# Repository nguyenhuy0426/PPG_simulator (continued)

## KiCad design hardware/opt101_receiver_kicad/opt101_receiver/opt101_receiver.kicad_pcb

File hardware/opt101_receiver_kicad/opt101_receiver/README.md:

> Gá mới: thanh chữ U không bắt vít, hai biến thể riêng theo receiver. Xem `mechanical/README.md`.

# PCB thu PPG — OPT101P ×2, 70 × 20 mm

Mở **`opt101_receiver.kicad_pro` bằng KiCad 10**, rồi mở schematic hoặc PCB.
Thiết kế đã đi dây hai lớp, có thư viện symbol, footprint và mô hình 3D cục bộ.
Ảnh `reports/pcb_top.png` hiển thị **socket trống**, chưa cắm IC OPT101P.
Mặt sau có silkscreen `DATN: PPG-Simulator` và
`Nguyen Nhat Huy - Pham Thanh Vy`; xem `reports/pcb_bottom.png`.
Mặt sau cũng ghi tên tín hiệu tại từng pad J1/J2/J3 và từng hàng chân của
hai socket OPT101. Các nhãn này không dùng số thứ tự chân; `R/I` là hai đầu
ra, `V` là 3,3 V, `GR/GI` là ground theo kênh, `FB` là hồi tiếp và `NC` để hở.

## Linh kiện và kết nối

| Ref | Linh kiện / quy cách | Số lượng |
|---|---|---:|
| U1, U2 | OPT101P dạng PDIP-8, cắm socket DIP-8 rộng 7,62 mm, bước chân 2,54 mm | 2 IC + 2 socket |
| C1, C2 | Tụ gốm dán **100 nF, 50 V, X7R, 0805**, không phân cực | 2 |
| R1, R2 | 1 kΩ 1%, SMD 0805, lọc ngõ ra | 2 |
| C3, C4 | 1 µF X7R 16 V, SMD 0805, không phân cực | 2 |
| J1, J2 | Header đực thẳng 1×4, bước 2,00 mm | 2 |
| J3 | Header đực thẳng 1×2, bước 2,54 mm | 1 |

Socket chỉ nhận **PDIP có chân xuyên lỗ**. OPT101 dạng SOP chân cong J không
cắm trực tiếp được. Đối chiếu package thực trước khi tháo IC khỏi module tím.
Rãnh socket và dấu pin 1 của IC hướng về cạnh trên có chữ RED/A2, IR/A0.

U1 là **Red → A2**, U2 là **IR → A0**. Với từng IC:

- Chân 1 → nguồn 3,3 V từ Grove; tụ 100 nF nối nguồn với GND ngay cạnh socket.
- Chân 3 và 8 → GND.
- Chân 4 nối trực tiếp chân 5 bằng đường đồng để dùng hồi tiếp 1 MΩ trong IC.
- Chân 2, 6, 7 để hở có chủ ý; không gắn điện trở 1 MΩ ngoài.

**J1/J2**, đọc theo số pad, từ pad vuông sang phải khi nhìn mặt linh kiện:

| Chân | J1 → socket A2 trên HAT | J2 → socket A0 trên HAT |
|---|---|---|
| 1 — SIG | OUT_RED | OUT_IR |
| 2 — NC | Không nối | Không nối |
| 3 — 3V3 | Nguồn 3,3 V | Nguồn 3,3 V |
| 4 — GND | GND | GND |

Pinout theo chuẩn Grove analog: pin 1 tín hiệu chính, pin 2 tín hiệu phụ,
pin 3 nguồn, pin 4 GND. Đây là **header trần bước 2 mm**, không phải socket
Grove có khóa. Kiểm tra thứ tự dây đến HAT trước khi cắm; không suy ra chiều
cắm chỉ từ màu dây. Chân phụ A1/A3 không được nối vào mạch.

C1/C2 là tụ bypass nguồn, **không phân cực**. Điện áp mạch chỉ 3,3 V nhưng
chọn loại 50 V X7R cỡ 0805. Loại 25 V X7R cỡ 0805 cũng dùng được về điện;
không thay bằng tụ điện phân vì tác dụng bypass cao tần khác nhau.

Mỗi kênh có đường nguồn và vùng GND riêng trên PCB; hai GND chung tại HAT.
Cắm cả hai cáp Grove để cấp nguồn đủ hai kênh. Không cấp 5 V vào board.

**J3 cho ADS1115**:

| Chân | Tín hiệu | Cách nối dự kiến |
|---|---|---|
| 1 — pad vuông, RED | OUT_RED, sau R1, cùng net J1.1 | ADS1115 AIN0 |
| 2 — IR | OUT_IR, sau R2, cùng net J2.1 | ADS1115 AIN1 |

J3 là ngõ lấy tín hiệu song song, không có buffer, không có nguồn hoặc GND.
ADS1115 cần được cấp nguồn riêng phù hợp và **nối GND về cùng GND HAT/Pi**.
Việc cấp nguồn OPT101 vẫn qua J1/J2. Hai đầu ra không phải một cặp vi sai:
đọc từng kênh so với GND. Cấu hình ADC, I²C và phần mềm ADS1115 chưa thuộc
thiết kế này. Nên dùng dây tín hiệu ngắn, đi sát dây GND; tải của ADC/cáp và
việc đọc đồng thời với Grove chưa được thử trên phần cứng.

## Kích thước và khớp mô hình 3D

PCB v1.5: **70 × 20 × 1,6 mm**, không có lỗ bắt vít. Tính từ góc trên trái:
- Tâm OPT101: (15,75; 7,81) và (54,25; 7,81) mm.
- J1/J2: chân đầu tại X=13/51 mm, Y=16,5 mm; bước 2 mm.
- J3: X=26/28,54 mm, Y=16,5 mm.

Đường đồng ngang/dọc; R1/R2 và C3/C4 ở mặt sau, C1/C2 sát socket ở mặt trước.
Gá riêng `mechanical/frame_70x20_print.stl` giữ mặt PCB tại X thế giới 137,5 mm,
bậc đỡ Y=19,81 mm; tâm quang vẫn Y=32 mm, Z=±19,25 mm. Hai kênh cách 38,5 mm.
Gá không bắt vít; giữ board và bịt khe/vách giữa bằng băng keo cách điện đục quang.
Không dùng gá BPW34 thay gá OPT101 vì vị trí cảm biến theo cạnh ngắn khác nhau.

### Kiểm tra đường ánh sáng và khẩu độ

Kiểm tra boolean dùng trực tiếp STL thân hộp, nắp, các tấm khẩu độ và khung PCB
mới đạt **20/20 phép thử hình học**. Ở vị trí danh nghĩa, trục của LED Red và
IR đều đi qua tâm lỗ khẩu độ tại X = 114,2 mm rồi đến tâm vùng nhạy của OPT101
tương ứng. Tia thẳng từ LED này hướng tới cảm biến kia cắt vách ngăn đặc giữa
hai buồng, nên không có đường nhìn thẳng xuyên kênh.

- Tấm `blank` chặn tia trục của cả hai kênh.
- Lỗ Ø2, Ø5 và Ø16 đều cho tia trục đi qua.
- Vùng nhạy OPT101 là 2,29 × 2,29 mm. Khi chiếu ngược các góc vùng nhạy lên
  mặt khẩu độ, bán kính góc lớn nhất là khoảng 0,99 mm cho Red và 1,40 mm cho
  IR. Vì vậy Ø2 chỉ vừa đủ cho Red và cắt các góc vùng nhạy IR; **Ø5 hoặc Ø16
  phủ toàn bộ vùng nhạy danh nghĩa của cả hai kênh**.
- Bán kính chùm tại mức nửa cường độ trong mô hình nguồn lớn hơn các lỗ khẩu
  độ, nên khẩu độ chủ động giới hạn lượng sáng. Kiểm tra này xác nhận đường
  nhìn và độ phủ hình học, không dự đoán công suất quang hoặc biên độ tín hiệu.

Kết luận phụ thuộc vào tâm package danh nghĩa và khoảng X cửa sổ cảm biến
126,5–132,0 mm lấy từ bao socket + IC. Sai số tâm die, chiều cao socket thật,
độ trong của nhựa in, phản xạ mặt trong và khe lắp chưa được mô phỏng. Sau khi
in cần thử lần lượt với tấm `blank` và Ø5: `blank` phải cho mức tối gần như nhau
khi LED bật/tắt, còn Ø5 phải tạo đáp ứng rõ chỉ ở đúng kênh.

### Thay đổi mốc khoảng cách quang

Mô hình cũ đặt cửa sổ module tại X = 120 mm nhờ module tím và trụ đỡ.
Cắm IC trực tiếp lên socket của PCB **không giữ nguyên mốc 120 mm**.
Gọi `h` là khoảng cách đo vuông góc từ mặt linh kiện PCB đến cửa sổ quang
của IC đã cắm hết vào socket:

```
X_cửa_sổ_mới = 137,5 - h
d_thực = d_theo_thang_cũ + 17,5 - h
```

Ví dụ **chỉ để minh họa**, nếu đo h = 8,3 mm thì d thực tăng 9,2 mm.
Không dùng ví dụ này như kích thước bảo đảm của socket. Mã mô hình cũ và
thang khoảng cách cũ chưa được đổi; phải đo lại h và hiệu chuẩn khoảng cách.
Không đưa board ra trước để cố giữ X=120 vì board liền sẽ đụng vách ngăn giữa.

## Kiểm tra và giới hạn

Kiểm tra bằng **KiCad 10.0.6**: ERC 0 lỗi/0 cảnh báo; DRC 0 vi phạm,
0 pad chưa nối, 0 lỗi parity; 152 kiểm tra hợp đồng chân, kích thước,
hình học đường đồng đạt.
Kiểm tra cơ khí: 386/386 đạt với bao linh kiện đã nêu; khung là một khối kín.
Kiểm tra đường quang danh nghĩa: 20/20 đạt.

- `reports/erc.rpt`: ERC schematic.
- `reports/drc.rpt`: DRC, vùng đồng đã đổ, kiểm tra parity với schematic.
- `reports/pin_contract.json`: kiểm tra độc lập chân điện, bước header/socket,
  kích thước board và khoảng cách hai làn.
- `mechanical/fit_report.json`: kiểm tra boolean với **STL thân/nắp đã xuất
  trong source**, gồm đường đưa cụm từ trên xuống theo bước 2 mm.
- `mechanical/optical_report.json`: kết quả định lượng đường tia, độ che của
  từng khẩu độ và chặn tia chéo giữa hai kênh.
- `mechanical/optical_alignment.png`: hình diễn giải vị trí LED, khẩu độ và
  khoảng cửa sổ OPT101 theo trục X.

Kiểm tra cơ khí dùng bao linh kiện: socket + IC cao tối đa 11 mm, header
cao tối đa 12 mm, tụ cao tối đa 7 mm phía trước PCB. Chọn linh kiện trong
các bao này. Đầu cáp mềm chưa được mô hình hóa. Kiểm tra CAD không thay thế
thử lắp bản in, kiểm tra rò sáng, đo điện hoặc hiệu chuẩn quang thực tế.

Các kết quả phần cứng chưa thực hiện: nguồn thật, cắm socket, mức tín hiệu,
nhiễu, bão hòa, Grove ADC và ADS1115. ERC/DRC sạch không phải chứng minh
đã đo được tín hiệu PPG trên mạch thật.

## File gia công

`fabrication/` chứa Gerber hai lớp đồng, soldermask hai mặt, silkscreen và
Edge.Cuts, kèm Excellon tách PTH/NPTH. Số lượng/cỡ lỗ khoan theo `reports/drill.rpt`; receiver không còn lỗ bắt vít. Chọn FR4 dày 1,6 mm,
đồng 1 oz, 70 × 20 mm; không yêu cầu trở kháng kiểm soát.
File này đã xuất nhưng **chưa được gửi đặt sản xuất**. Kiểm tra package IC,
socket, đầu cáp và bản in khung thật trước khi chốt gia công.

## Tái sinh

Không cần chạy script để mở hoặc chỉnh file trong KiCad. `generate_design.py`
**ghi đè** thiết kế đã sinh; chỉ chạy lại nếu muốn tái tạo từ mã tham số.

```bash
python-with-pcbnew generate_design.py --kicad-share /path/to/share/kicad --cli /path/to/kicad-cli
kicad-cli sch erc opt101_receiver.kicad_sch -o reports/erc.rpt
kicad-cli pcb drc opt101_receiver.kicad_pcb --refill-zones --save-board --schematic-parity -o reports/drc.rpt
python-with-pcbnew verify_design.py
# Từ gốc repository:
.cad_venv/bin/python hardware/opt101_receiver_kicad/opt101_receiver/mechanical/build_adapter.py
.cad_venv/bin/python hardware/opt101_receiver_kicad/opt101_receiver/mechanical/optical_check.py
```

Nguồn kỹ thuật:

- [TI OPT101 datasheet, pinout và hồi tiếp](https://www.ti.com/lit/ds/symlink/opt101.pdf), trang 3, 13 và 23.
- [Seeed Grove System](https://wiki.seeedstudio.com/Grove_System/), pinout Grove analog.
- [Grove Base HAT for Raspberry Pi](https://wiki.seeedstudio.com/Grove_Base_Hat_for_Raspberry_Pi/), analog 3,3 V.
- Sơ đồ gốc: `docs/hardware/PPG_PROTOTYPE_SCHEMATIC.md`, phần RX.

Footprint và mô hình 3D được sao chép từ thư viện KiCad 10, đổi tên thư viện
thành PPG và dùng đường dẫn tương đối để dự án có thể chuyển máy.
Thư viện KiCad dùng CC-BY-SA 4.0 với ngoại lệ sử dụng trong thiết kế điện tử:
[KiCad Library License](https://www.kicad.org/libraries/license/).

## Schematic v1.5 — lọc ngõ ra

Hai kênh được vẽ bằng dây nối trực tiếp từ Grove qua nguồn/bypass tới OPT101,
strap 4–5, rồi qua R1/R2 = 1 kΩ tới Grove/J3; C3/C4 = 1 µF nối từ OUT sau điện trở xuống GND từng kênh. Bộ lọc có fc danh nghĩa 159 Hz, suy hao khoảng 0,8% tại 20 Hz; không phải lọc notch 50 Hz. Với nguồn 3,3 V, OPT101 không rail-to-rail: cần chừa headroom khoảng 1,15–1,3 V phía nguồn dương. Xem `reports/schematic.pdf` và `reports/schematic.png`. Giao cắt không
có dấu chấm không nối điện.

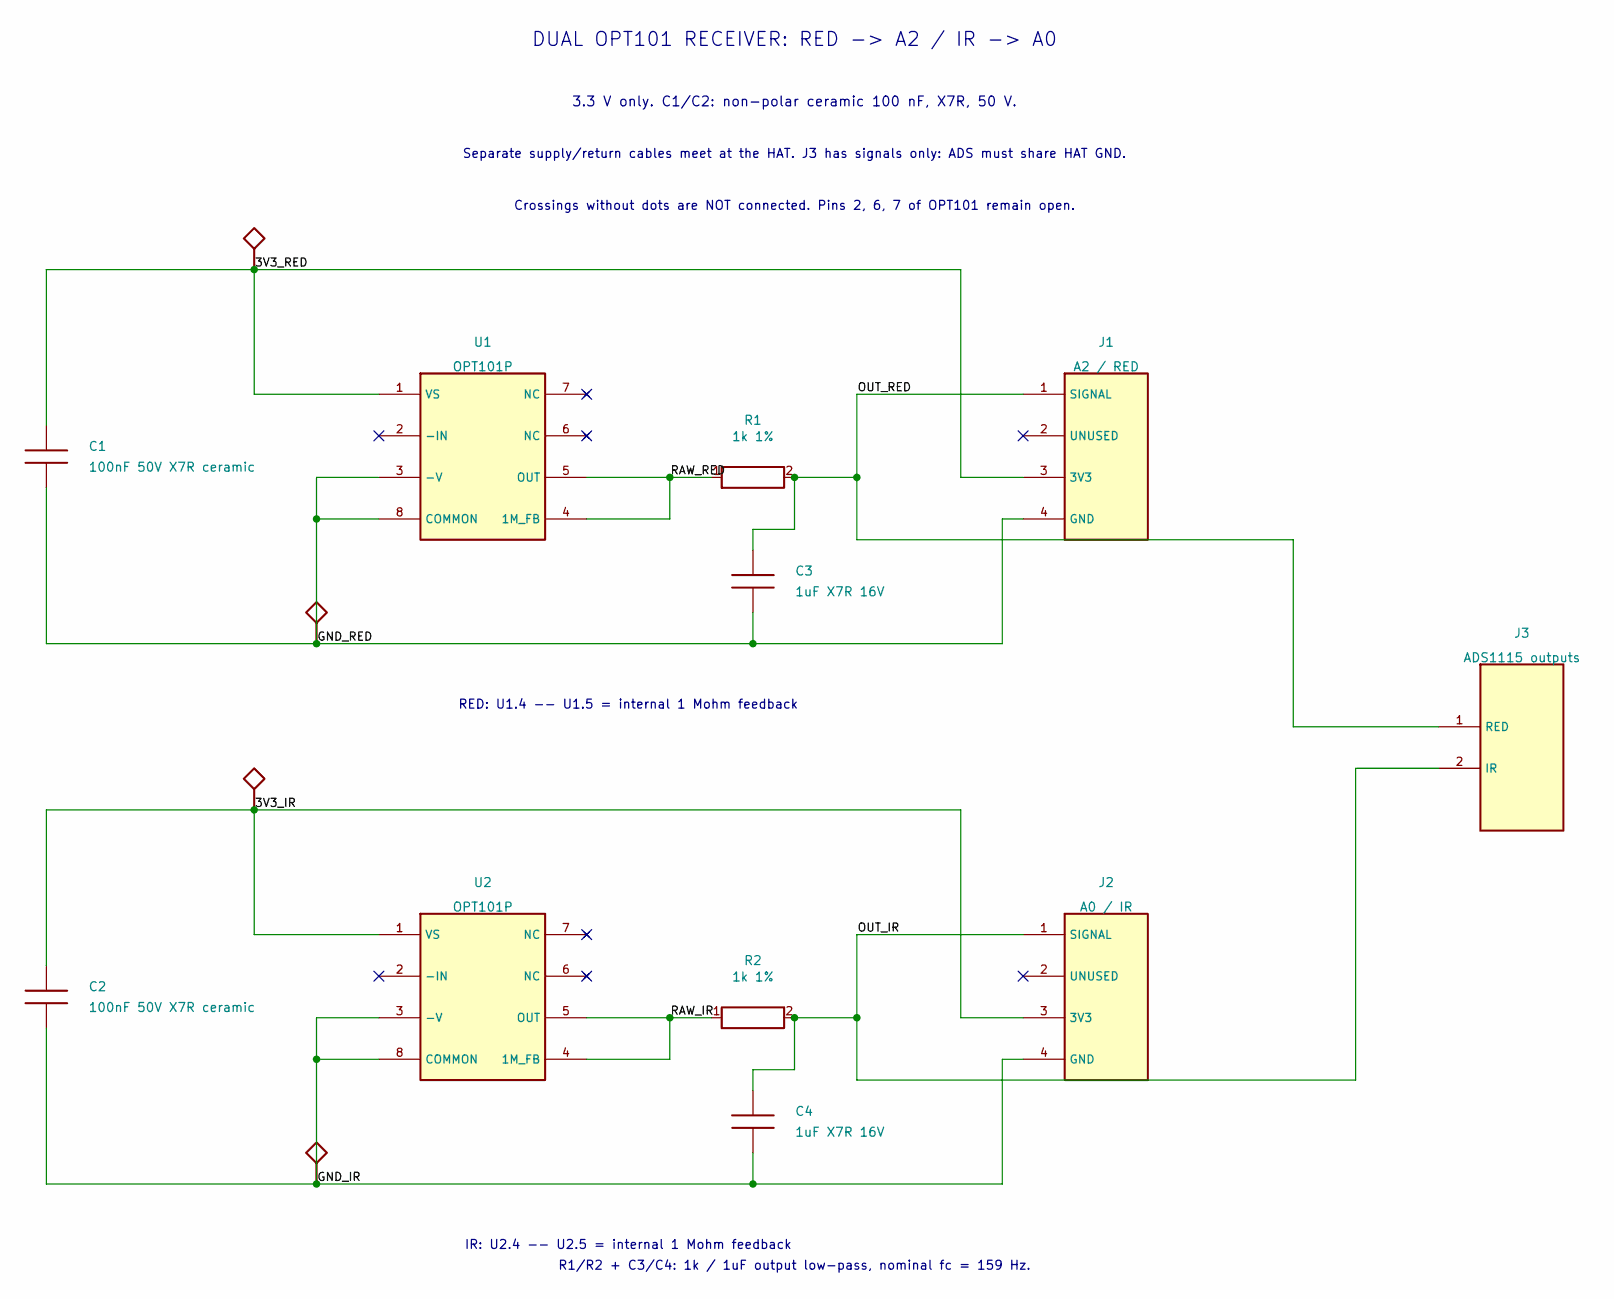
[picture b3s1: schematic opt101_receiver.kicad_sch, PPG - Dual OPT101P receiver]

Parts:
C1, C2: 100nF 50V X7R ceramic; C0805_Hand
C3, C4: 1uF X7R 16V; C0805_Hand
J1: A2 / RED; Header_1x04_P2mm
J2: A0 / IR; Header_1x04_P2mm
J3: ADS1115 outputs; Header_1x02_P2.54mm
R1, R2: 1k 1%; R0805_Hand
U1, U2: OPT101P; DIP8_Socket

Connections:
/3V3_IR: C2.1, J2.3 (3V3), U2.1 (VS)
/3V3_RED: C1.1, J1.3 (3V3), U1.1 (VS)
/GND_IR: C2.2, C4.2, J2.4 (GND), U2.3 (-V), U2.8 (COMMON)
/GND_RED: C1.2, C3.2, J1.4 (GND), U1.3 (-V), U1.8 (COMMON)
/OUT_IR: C4.1, J2.1 (SIGNAL), J3.2 (IR), R2.2
/OUT_RED: C3.1, J1.1 (SIGNAL), J3.1 (RED), R1.2
/RAW_IR: R2.1, U2.4 (1M_FB), U2.5 (OUT)
/RAW_RED: R1.1, U1.4 (1M_FB), U1.5 (OUT)

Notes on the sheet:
RED: U1.4 -- U1.5 = internal 1 Mohm feedback
IR: U2.4 -- U2.5 = internal 1 Mohm feedback
DUAL OPT101 RECEIVER: RED -> A2 / IR -> A0
3.3 V only. C1/C2: non-polar ceramic 100 nF, X7R, 50 V.
Separate supply/return cables meet at the HAT. J3 has signals only: ADS must share HAT GND.
Crossings without dots are NOT connected. Pins 2, 6, 7 of OPT101 remain open.
R1/R2 + C3/C4: 1k / 1uF output low-pass, nominal fc = 159 Hz.

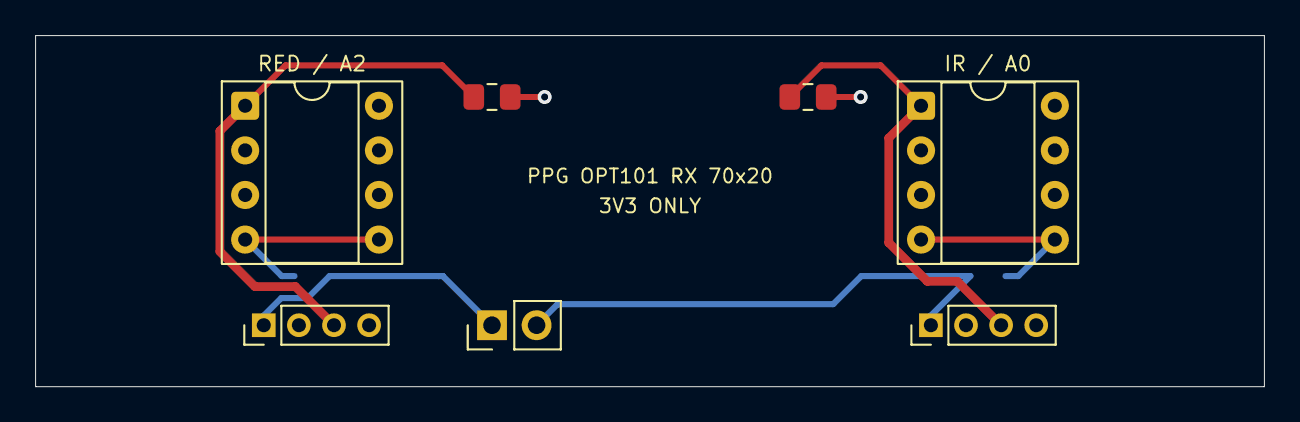
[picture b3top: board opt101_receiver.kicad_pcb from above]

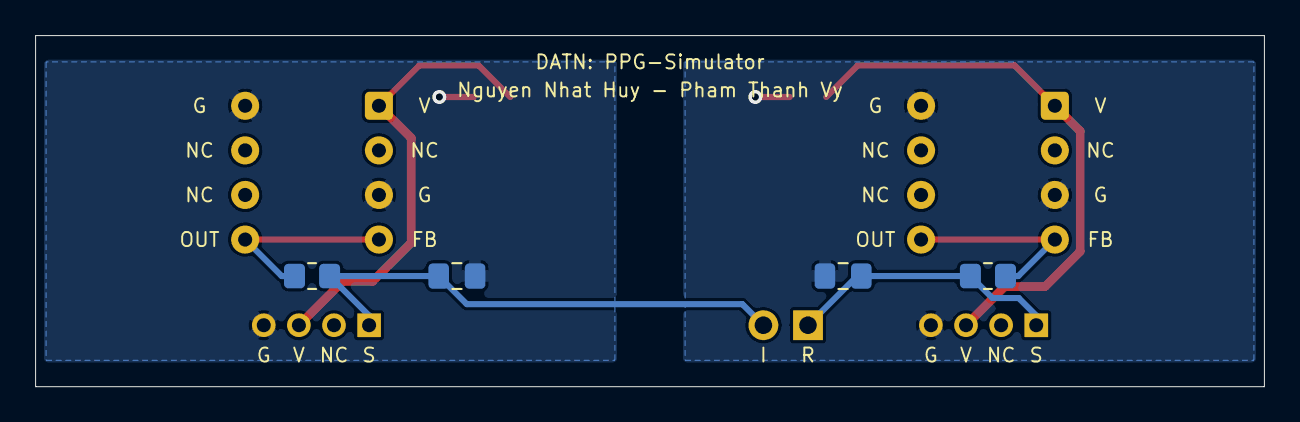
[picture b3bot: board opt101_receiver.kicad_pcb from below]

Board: 2 copper layers, 70.0 x 20.0 mm, 11 parts (4 on the bottom side), 8 nets.

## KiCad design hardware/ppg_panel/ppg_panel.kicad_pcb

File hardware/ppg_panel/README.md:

# Official OPT101 + LED/IR driver panel

Open `ppg_panel.kicad_pro` in KiCad 10. This 70 × 60 mm, 1.6 mm thick,
two-layer panel contains one 70 × 20 mm OPT101 receiver and one 70 × 40 mm
shared-I²C LED/IR driver. Their nets are isolated. BPW34 is not included.

The outer rectangle is `Edge.Cuts`. One full-width V-score centre line is on
`Cmts.User`, 20 mm from the top (KiCad Y = 70 mm); it is not a milled slot.
Separate the bare boards before assembly. Confirm V-score depth, tolerances,
clearances and pricing for two designs with the board house.

To rebuild from the two source PCB files, run `build_panel.py` with KiCad 10
Python, then run `verify_panel.py` and KiCad DRC. The manifest records source
hashes. The independent audit checks source parity, electrical separation and
copper clearance from the score; CAD checks do not qualify a physical board.

The driver restores v1.9 and does not include later v2.0 manufacturing-rule
changes. Old three-board Gerbers and assembly files are obsolete and have
been removed. Verify current fabrication requirements, then regenerate and
inspect the panel Gerbers and drills before ordering.

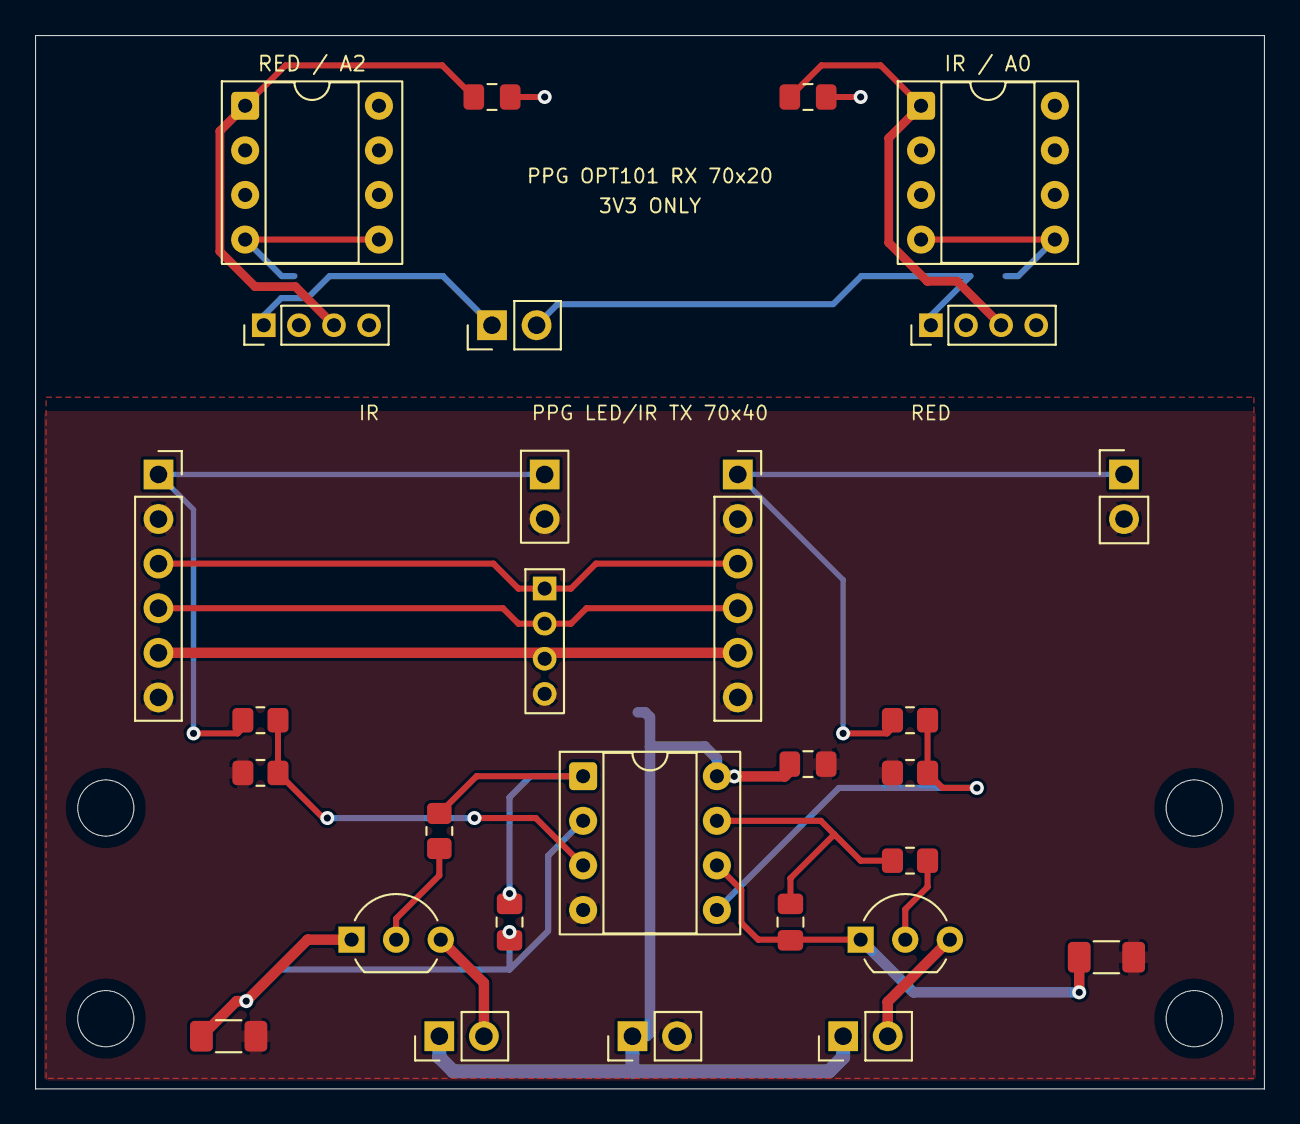
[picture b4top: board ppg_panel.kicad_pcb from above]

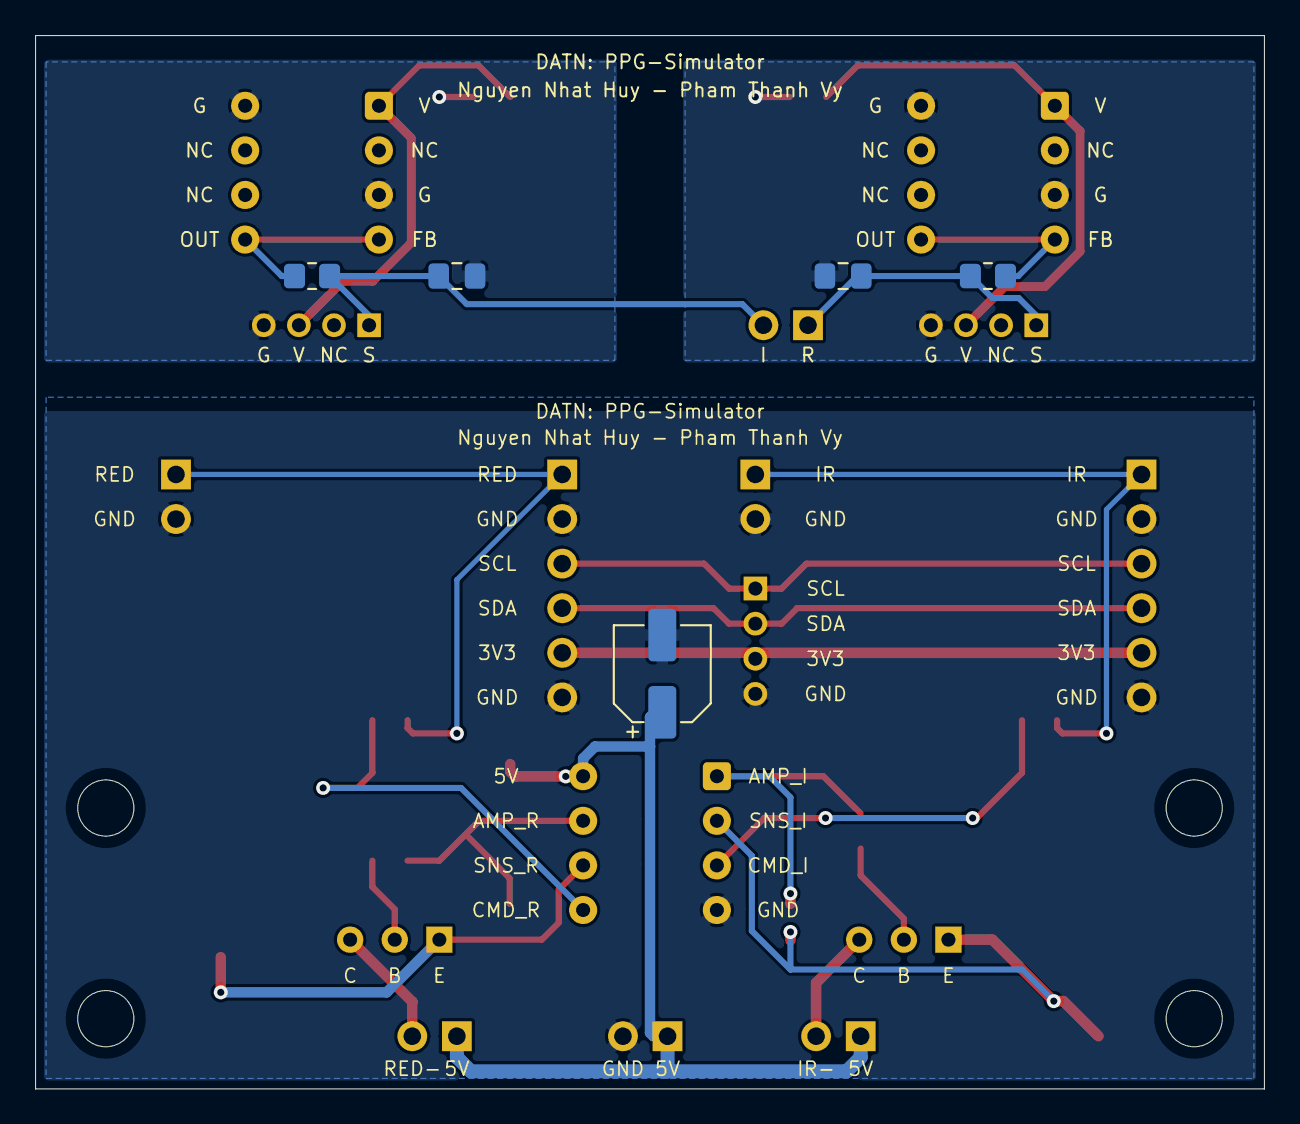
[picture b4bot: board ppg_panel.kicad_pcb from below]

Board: 2 copper layers, 70.0 x 60.0 mm, 37 parts (5 on the bottom side), 25 nets.

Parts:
OPT_C1, OPT_C2: 100nF 50V X7R ceramic; C0805_Hand
OPT_C3, OPT_C4: 1uF X7R 16V; C0805_Hand
OPT_J1: A2 / RED; Header_1x04_P2mm
OPT_J2: A0 / IR; Header_1x04_P2mm
OPT_J3: ADS1115 outputs; Header_1x02_P2.54mm
OPT_R1, OPT_R2: 1k 1%; R0805_Hand
OPT_U1, OPT_U2: OPT101P; DIP8_Socket
TX_C2, TX_C4: DNP loop comp; C
TX_C5: 100nF X7R 50V; C
TX_C7: 10uF 16V; CP
TX_H1, TX_H2, TX_H3, TX_H4: M3 / 3.2mm; Hole
TX_J1: MCP4725 IR 0x60; Socket6
TX_J2: PI I2C INPUT / IR OUT; HeaderMixed
TX_J3: MCP4725 RED 0x61; Socket6
TX_J4: RED DAC OUT / GND; Header2
TX_J5: IR LED A / K; Header2
TX_J6: RED LED A / K; Header2
TX_J7: 5V INPUT / GND; Header2
TX_Q1, TX_Q2: 2N4401 / E-B-C; NPN
TX_R1, TX_R2, TX_R6, TX_R7: 10k 1%; R
TX_R3, TX_R8: 1k; R
TX_R4, TX_R9: 100R 1% 0.25W; RSense
TX_U1: LM358P / DIP8 socket; DIP8

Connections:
OPT/3V3_IR: OPT_C2.1, OPT_J2.3, OPT_U2.1
OPT/3V3_RED: OPT_C1.1, OPT_J1.3, OPT_U1.1
OPT/GND_IR: OPT_C2.2, OPT_C4.2, OPT_J2.4, OPT_U2.3, OPT_U2.8
OPT/GND_RED: OPT_C1.2, OPT_C3.2, OPT_J1.4, OPT_U1.3, OPT_U1.8
OPT/OUT_IR: OPT_C4.1, OPT_J2.1, OPT_J3.2, OPT_R2.2
OPT/OUT_RED: OPT_C3.1, OPT_J1.1, OPT_J3.1, OPT_R1.2
OPT/RAW_IR: OPT_R2.1, OPT_U2.4, OPT_U2.5
OPT/RAW_RED: OPT_R1.1, OPT_U1.4, OPT_U1.5
TX/3V3: TX_J1.5, TX_J2.5, TX_J3.5
TX/5V: TX_C5.1, TX_C7.1, TX_J5.1, TX_J6.1, TX_J7.1, TX_U1.8
TX/AMP_IR: TX_C2.1, TX_R3.1, TX_U1.1
TX/AMP_RED: TX_C4.1, TX_R8.1, TX_U1.7
TX/BASE_IR: TX_Q1.2, TX_R3.2
TX/BASE_RED: TX_Q2.2, TX_R8.2
TX/CMD_IR: TX_R1.2, TX_R2.1, TX_U1.3
TX/CMD_RED: TX_R6.2, TX_R7.1, TX_U1.5
TX/DAC_IR: TX_J1.1, TX_J2.1, TX_R1.1
TX/DAC_RED: TX_J3.1, TX_J4.1, TX_R6.1
TX/GND: TX_C5.2, TX_C7.2, TX_J1.2, TX_J1.6, TX_J2.2, TX_J2.6, TX_J3.2, TX_J3.6, TX_J4.2, TX_J7.2, TX_R2.2, TX_R4.2, TX_R7.2, TX_R9.2, TX_U1.4
TX/LED_K_IR: TX_J5.2, TX_Q1.3
TX/LED_K_RED: TX_J6.2, TX_Q2.3
TX/SCL: TX_J1.3, TX_J2.3, TX_J3.3
TX/SDA: TX_J1.4, TX_J2.4, TX_J3.4
TX/SENSE_IR: TX_C2.2, TX_Q1.1, TX_R4.1, TX_U1.2
TX/SENSE_RED: TX_C4.2, TX_Q2.1, TX_R9.1, TX_U1.6

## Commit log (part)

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2026-04-27 change the waveform PPG effect by BW, AM, FM
2026-04-27 upload PPG simulator
2026-04-27 update docs
2026-04-27 replace 2 button up/down into POT and update .md file
2026-04-27 Revise README for PPG Signal Simulator
    Updated README to reflect project title and remove outdated English version description.
2026-04-28 1.ble
2026-05-01 add module simulator to device raspi4
2026-05-02 add feature save data in csv file, fix display noise clearly.
2026-05-07 create a test dac for rasp by esp32s3 using adc gpio4,5--fix the button handler and pot
2026-05-10 create ble module, redesign ui without pot physic, using control by slider.
2026-05-12 change AC, DC amplitude
2026-05-14 add function record data and playback, change the UI using tkinter
2026-05-14 update MedicalSimulator submodule
2026-05-14 update readme.md file
2026-05-15 add run button
2026-05-15 test module
2026-05-16 Adjust the number increments in playback data.
2026-05-18 reduce amplitude of PPG signal
2026-05-22 change the amplitude of waveform PPG (DC and AC component)
2026-05-22 plot data
2026-05-22 add gitignore
2026-05-22 remove dataset from repository
